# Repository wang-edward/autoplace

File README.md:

# Autoplace
This is a kicad plugin to help in the intial layout of a board. It "solves" a component placement by minimizing wirelength while smoothing out density.

This isn't meant to one-shot a component layout, but as a helpful first step to group related components.

**It works best when Edge.Cuts is well defined, and static components (like ports) are locked.**

## Installation
Symlink `autoplace/` into the plugins folder:

### MacOS
```bash
ln -s "$(pwd)/autoplace" ~/Documents/KiCad/10.0/plugins/autoplace  # KiCad 10
```

### Linux
```bash
ln -s "$(pwd)/autoplace" ~/.local/share/KiCad/10.0/plugins/autoplace  # KiCad 10
```

The idea is based on the DreamPlace algorithm: https://github.com/limbo018/DREAMPlace

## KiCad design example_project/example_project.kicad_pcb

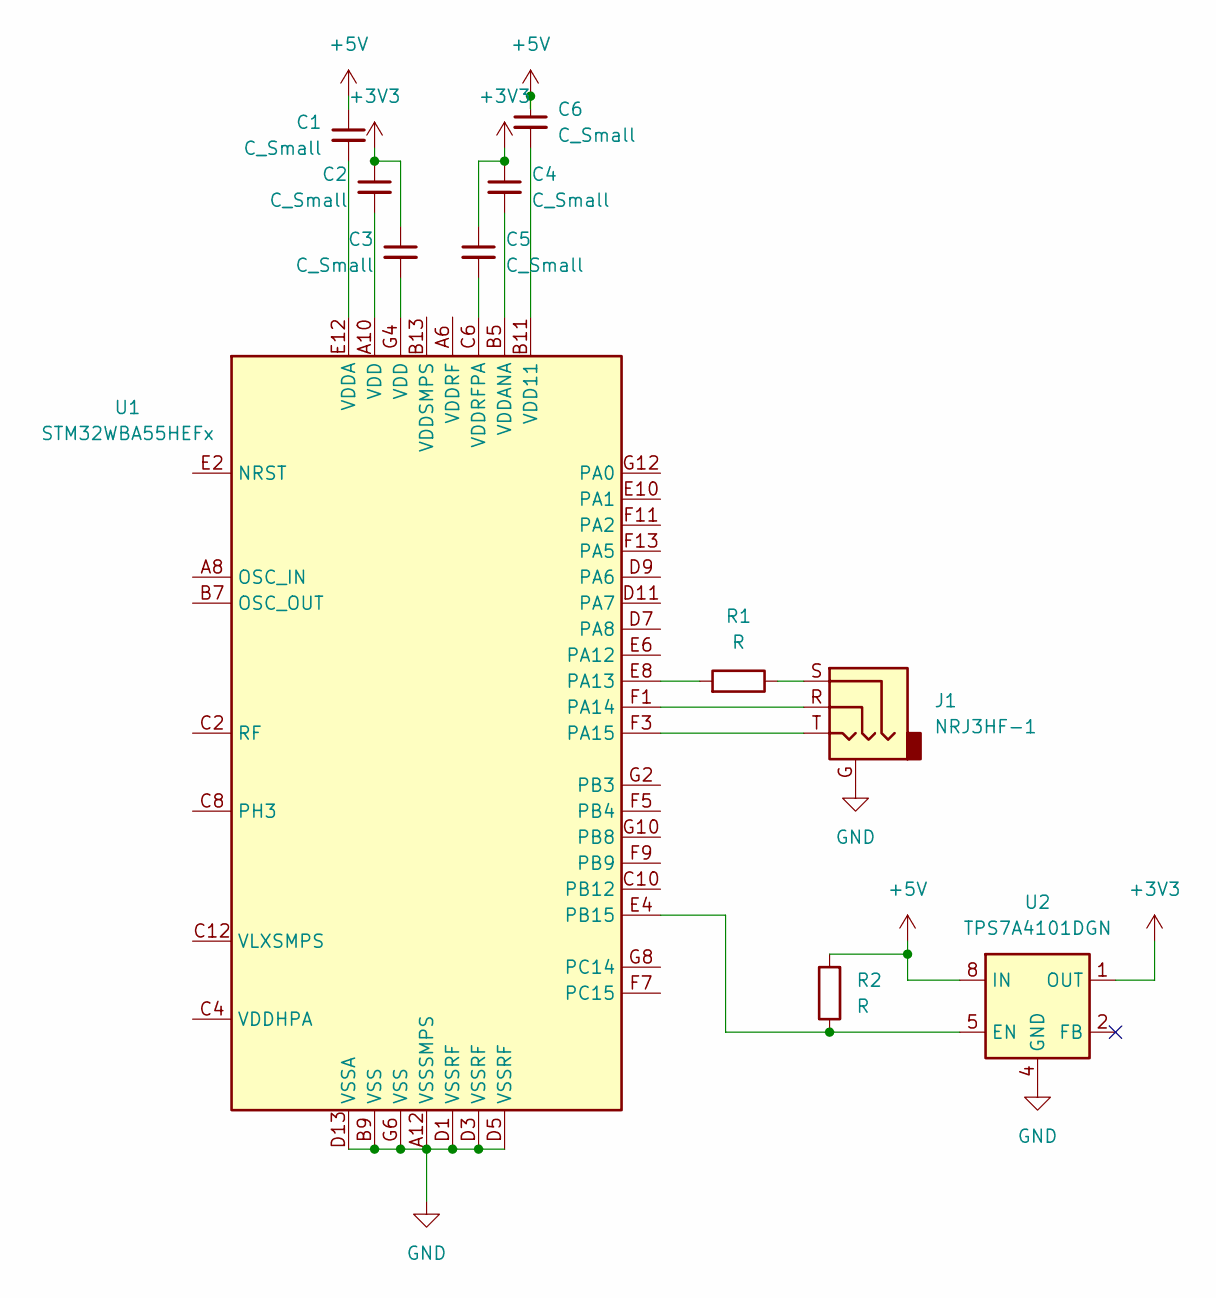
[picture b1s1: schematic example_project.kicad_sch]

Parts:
C1, C2, C3, C4, C5, C6: C_Small; C_0805_2012Metric
J1: NRJ3HF-1; Jack_6.35mm_Neutrik_NRJ3HF-1_Horizontal
R1, R2: R; R_0805_2012Metric
U1: STM32WBA55HEFx; ST_WLCSP-41_2.98x2.76mm_Layout13x7_P0.4mm_Stagger
U2: TPS7A4101DGN; Texas_DGN0008B_VSSOP-8-1EP_3x3mm_P0.65mm_EP2x3mm_Mask1.88x1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

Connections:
+3V3: C2.1, C3.1, C4.1, C5.1, U2.1 (OUT)
+5V: C1.1, C6.1, R2.2, U2.8 (IN)
GND: J1.G, U1.A12 (VSSSMPS), U1.B9 (VSS), U1.D1 (VSSRF), U1.D3 (VSSRF), U1.D5 (VSSRF), U1.D13 (VSSA), U1.G6 (VSS), U2.4 (GND), U2.9 (GND)
unnamed: C2.2, U1.A10 (VDD)
unnamed: C3.2, U1.G4 (VDD)
unnamed: J1.S, R1.1
unnamed: R1.2, U1.E8 (PA13)
unnamed: J1.R, U1.F1 (PA14)
unnamed: J1.T, U1.F3 (PA15)
unnamed: R2.1, U1.E4 (PB15), U2.5 (EN)
unnamed: C6.2, U1.B11 (VDD11)
unnamed: C1.2, U1.E12 (VDDA)
unnamed: C4.2, U1.B5 (VDDANA)
unnamed: C5.2, U1.C6 (VDDRFPA)

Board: 2 copper layers, 11 parts (0 on the bottom side), 14 nets, no tracks yet.

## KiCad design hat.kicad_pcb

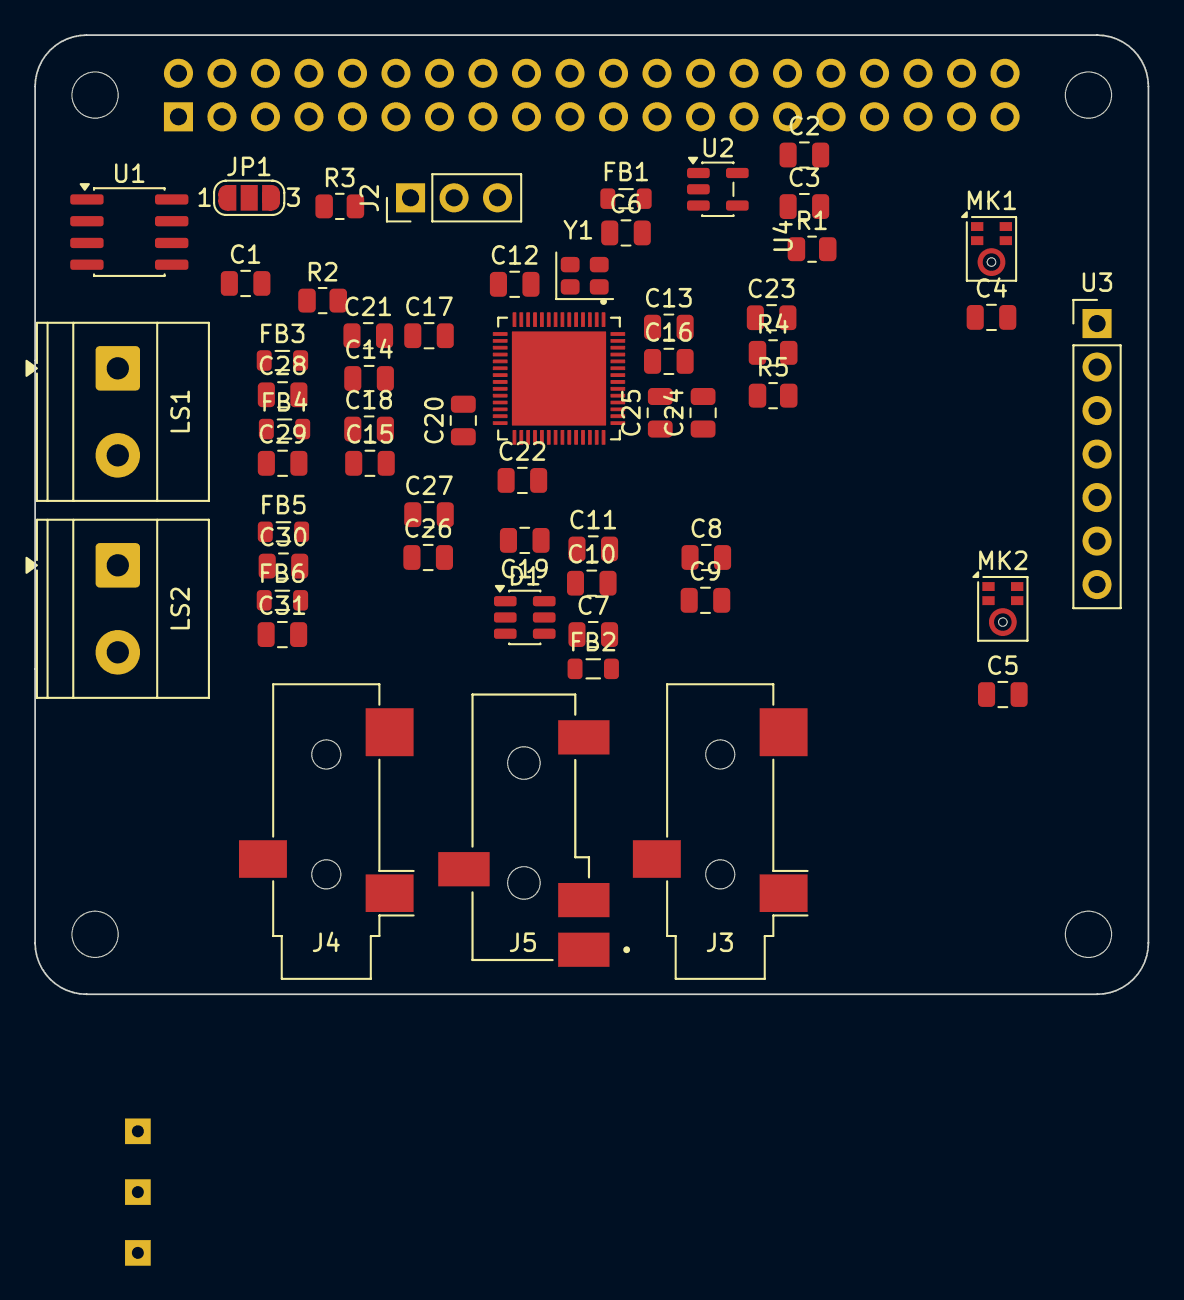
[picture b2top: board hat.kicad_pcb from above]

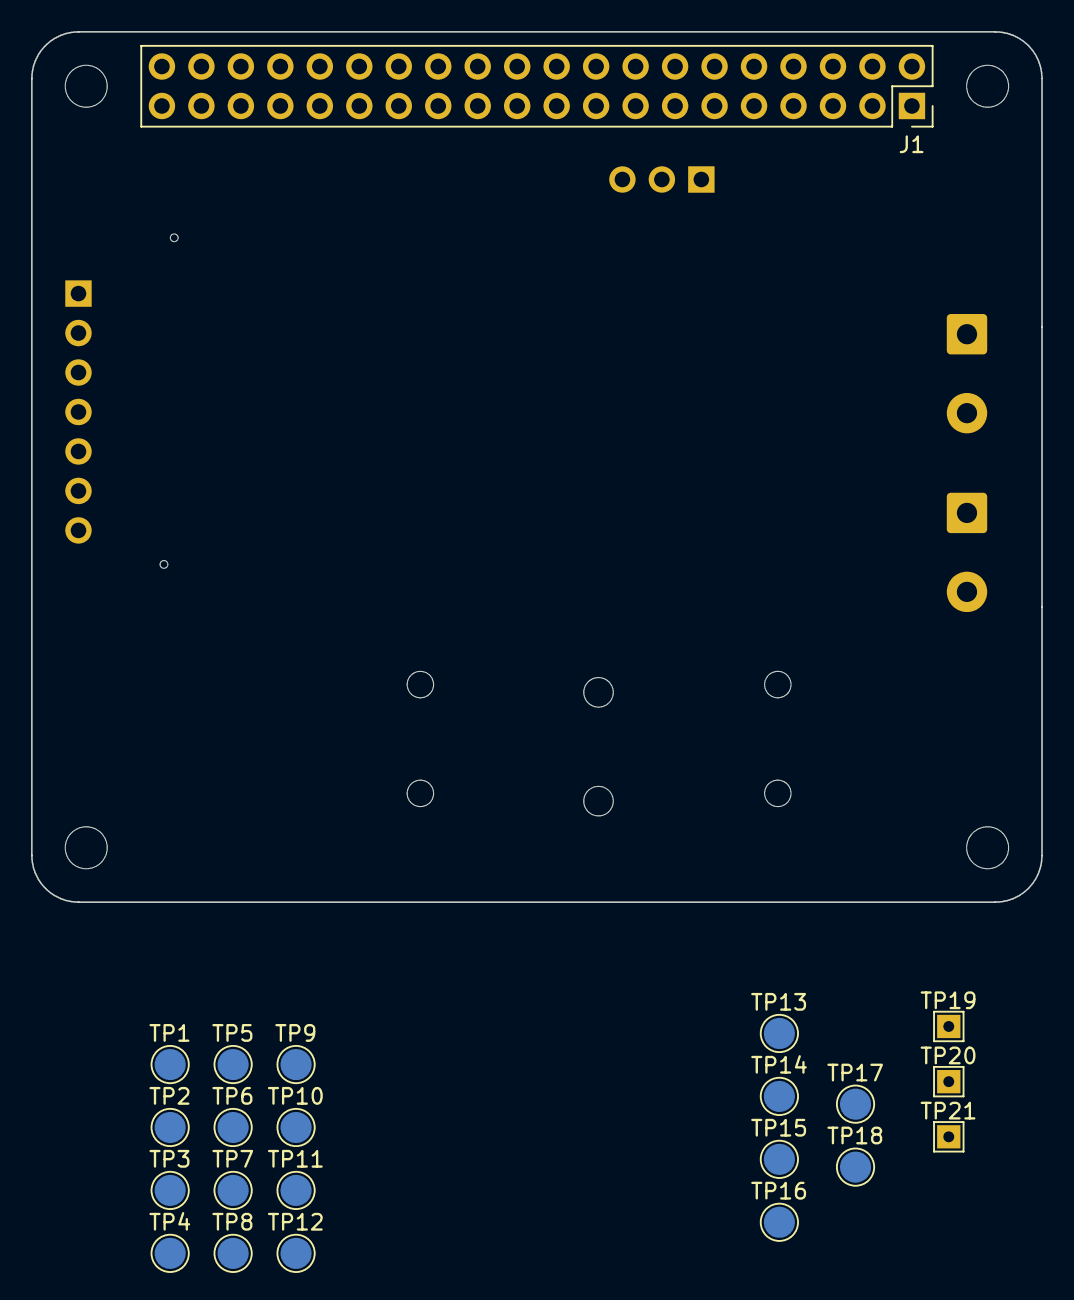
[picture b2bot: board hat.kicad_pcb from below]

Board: 2 copper layers, 65.0 x 56.0 mm, 83 parts (22 on the bottom side), 56 nets, no tracks yet.

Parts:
C1: 100n; C_0805_2012Metric
C2, C3, C8, C9, C10, C11, C13, C15, C16, C18, C19, C20, C21, C22, C24: 1uF; C_0805_2012Metric
C4, C5, C6: 0.1uF X7R; C_0805_2012Metric
C7: 47pF; C_0805_2012Metric
C12, C23: 0.1uF; C_0805_2012Metric
C14, C17, C26, C27: 10uF; C_0805_2012Metric
C25: 2.2uF; C_0805_2012Metric
C28, C29, C30, C31: 470pF; C_0805_2012Metric
D1: ESDA6V1BC6; SOT-23-6
FB1, FB2, FB3, FB4, FB5, FB6: 600Ohm@100MHz; L_0805_2012Metric
J1: GPIO; PinSocket_2x20_P2.54mm_Vertical
J2: Uart; PinHeader_1x03_P2.54mm_Vertical
J3: LineIn; Jack_3.5mm_CUI_SJ-3523-SMT_Horizontal
J4: LineOut; Jack_3.5mm_CUI_SJ-3523-SMT_Horizontal
J5: Headphone; CUI_SJ-43514-SMT-TR
JP1: ID_WP; SolderJumper-3_P1.3mm_Open_RoundedPad1.0x1.5mm_NumberLabels
LS1: SpeakerL; TerminalBlock_Phoenix_MKDS-1,5-2-5.08_1x02_P5.08mm_Horizont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
LS2: SpeakerR; TerminalBlock_Phoenix_MKDS-1,5-2-5.08_1x02_P5.08mm_Horizont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
MH1, MH2, MH3, MH4: MountingHole_2.7mm_M2.5
MK1: MicL; Knowles_LGA-5_3.5x2.65mm
MK2: MicR; Knowles_LGA-5_3.5x2.65mm
R1, R4: 10k; R_0805_2012Metric
R2, R3: 3.9k; R_0805_2012Metric
R5: 2.2k; R_0805_2012Metric
TP1: MICBIAS; TestPoint_Pad_D2.0mm
TP2: INA1; TestPoint_Pad_D2.0mm
TP3: INA2; TestPoint_Pad_D2.0mm
TP4: CODEC_MCLK; TestPoint_Pad_D2.0mm
TP5: MIC2P; TestPoint_Pad_D2.0mm
TP6: MIC2N; TestPoint_Pad_D2.0mm
TP7: HPSNS; TestPoint_Pad_D2.0mm
TP8: HPR; TestPoint_Pad_D2.0mm
TP9: HPL; TestPoint_Pad_D2.0mm
TP10: JACKSENSE; TestPoint_Pad_D2.0mm
TP11: RECP; TestPoint_Pad_D2.0mm
TP12: RECN; TestPoint_Pad_D2.0mm
TP13: SPKLP; TestPoint_Pad_D2.0mm
TP14: SPKLN; TestPoint_Pad_D2.0mm
TP15: SPKRP; TestPoint_Pad_D2.0mm
TP16: SPKRN; TestPoint_Pad_D2.0mm
TP17: LDO_IN; TestPoint_Pad_D2.0mm
TP18: LDO_OUT; TestPoint_Pad_D2.0mm
TP19: 5V; TestPoint_THTPad_1.5x1.5mm_Drill0.7mm
TP20: GND; TestPoint_THTPad_1.5x1.5mm_Drill0.7mm
TP21: 3V3; TestPoint_THTPad_1.5x1.5mm_Drill0.7mm
U1: CAT24C256; SOIC-8_3.9x4.9mm_P1.27mm
U2: TPS7A20xxxDBV; SOT-23-5
U3: Oled; PinHeader_1x07_P2.54mm_Vertical
U4: MAX98089ETN_T
Y1: 12.288MHz; Oscillator_SMD_SeikoEpson_SG210-4Pin_2.5x2.0mm

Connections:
+1V8: C3.1, C4.2, C5.2, C13.2, C14.2, C15.2, C16.2, MK1.5 (VDD), MK2.2 (SEL), MK2.5 (VDD), TP18.1 (1_1), U2.5 (OUT), U4.25 (PVDD), U4.50 (AVDD), U4.53 (DVDD)
+3V3: C1.1, C2.1, C12.2, C23.2, FB1.2, J1.1, J1.17, JP1.2 (B), R2.1, R3.1, R4.2, TP17.1 (1_1), TP21.1 (1_1), U1.8 (VCC), U2.1 (IN), U3.1 (VCC), U4.6 (DVDDS1), U4.55 (DVDDS2)
+5V: C17.2, C18.2, C21.2, J1.2, J1.4, TP19.1 (1_1), U4.18 (SPKRVDD), U4.19 (SPKLVDD)
/1V8_EN: J1.16, R1.1, U2.3 (EN)
/GPIO2/SDA1: J1.3, U4.52 (SDA)
/GPIO3/SCL1: J1.5, U4.51 (SCL)
/GPIO8/SPI0.CE0: J1.24, U3.5 (CS)
/GPIO10/SPI0.MOSI: J1.19, U3.3 (DIN)
/GPIO11/SPI0.SCLK: J1.23, U3.4 (CLK)
/GPIO14/TXD0: J1.8, J2.2
/GPIO15/RXD0: J1.10, J2.3
/GPIO17: J1.11, R4.1, U4.56 (~IRQ)
/GPIO18/PCM.CLK: J1.12, U4.8 (BCLKS1)
/GPIO19/PCM.FS: J1.35, U4.10 (LRCLKS1)
/GPIO20/PCM.DIN: J1.38, U4.7 (SDOUTS1)
/GPIO21/PCM.DOUT: J1.40, U4.9 (SDINS1)
/GPIO22: J1.15, Y1.1 (OE)
/GPIO25: J1.22, U3.6 (DC)
/GPIO27: J1.13, U3.7 (RST)
/ID_SCL: J1.28, R3.2, U1.6 (SCL)
/ID_SDA: J1.27, R2.2, U1.5 (SDA)
/codec/C1N: C20.1, U4.27 (C1N)
/codec/C1P: C20.2, U4.26 (C1P)
/codec/DIGMICCLK: MK1.4 (CLOCK), MK2.4 (CLOCK), U4.41 (MIC1N/DIGMICCLK)
/codec/DIGMICDATA: MK1.1 (DATA), MK2.1 (DATA), U4.40 (MIC1P/DIGMICDATA)
/codec/JackS: D1.6 (TVS4), FB2.1, J5.S, R5.2, TP1.1 (1_1), TP10.1 (1_1), U4.45 (JACKSNS)
GND: C1.2, C2.2, C3.2, C4.1, C5.1, C6.1, C7.2, C11.1, C12.1, C13.1, C14.1, C15.1, C16.1, C17.1, C18.1, C19.2, C21.1, C22.2, C23.1, C24.2, C25.2, C28.2, C29.2, C30.2, C31.2, D1.2 (COM), D1.4 (TVS3), D1.5 (COM), J1.6, J1.9, J1.14, J1.20, J1.25, J1.30, J1.34, J1.39, J2.1, J3.S, J4.S, J5.R2, MK1.2 (SEL), MK1.3 (GND), MK2.3 (GND), R1.2, TP7.1 (1_1), TP20.1 (1_1), U1.4 (GND), U2.2 (GND), U3.2 (GND), U4.3 (DGND), U4.16 (SPKRGND), U4.21 (SPKLGND), U4.30 (HPGND), U4.34 (HPSNS), U4.47 (AGND), U4.54 (SDINS2), U4.57 (EP), Y1.2 (GND)
unnamed: C8.1, J3.T
unnamed: C9.1, J3.R
unnamed: C7.1, C10.1, FB2.2
unnamed: C26.2, J4.T, TP11.1 (1_1)
unnamed: C27.2, J4.R, TP12.1 (1_1)
unnamed: C28.1, FB3.2, LS1.1, TP13.1 (1_1)
unnamed: C29.1, FB4.2, LS1.2, TP14.1 (1_1)
unnamed: C30.1, FB5.2, LS2.1, TP15.1 (1_1)
unnamed: C31.1, FB6.2, LS2.2, TP16.1 (1_1)
unnamed: D1.1 (TVS1), J5.T, TP9.1 (1_1), U4.33 (HPL)
unnamed: D1.3 (TVS2), J5.R1, TP8.1 (1_1), U4.35 (HPR)
unnamed: JP1.1 (A), U1.7 (WP)
unnamed: C22.1, U4.32 (HPVDD)
unnamed: C19.1, U4.31 (HPVSS)
unnamed: C10.2, TP5.1 (1_1), U4.39 (INA1/EXTMICP)
unnamed: C11.2, TP6.1 (1_1), U4.38 (INA2/EXTMICN)
unnamed: TP4.1 (1_1), U4.5 (MCLK), Y1.3 (OUT)
unnamed: C9.2, TP3.1 (1_1), U4.43 (MIC2N)
unnamed: C8.2, TP2.1 (1_1), U4.42 (MIC2P)
unnamed: R5.1, U4.44 (MICBIAS)
unnamed: C27.1, U4.23 (RECN/LOUTR/RXINN)
unnamed: C26.1, U4.24 (RECP/LOUTL/RXINP)
unnamed: C25.1, U4.48 (REF)
unnamed: C24.1, U4.49 (REG)
unnamed: FB4.1, U4.22 (SPKLN)
unnamed: FB3.1, U4.20 (SPKLP)
unnamed: FB6.1, U4.15 (SPKRN)
unnamed: FB5.1, U4.17 (SPKRP)
unnamed: C6.2, FB1.1, Y1.4 (Vcc)

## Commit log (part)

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2026-05-24 less code
2026-05-30 kicad import
2026-06-12 uv init and notebook
2026-06-12 attract
2026-06-12 wa_wirelength
2026-06-12 vibe
2026-06-12 vibe 2
2026-06-12 big thing and fixed
2026-06-12 wip theta
2026-06-12 something
2026-06-16 gitignore
2026-06-16 clean
2026-06-16 hello
2026-06-16 print
2026-06-16 get_edge_cuts
2026-06-16 get_components
2026-06-16 make example more complicated
2026-06-16 wip plugin
2026-06-16 desc2
2026-06-16 plugin showing up in toolbar!!!!!!!!!!!!!!!!!!
2026-06-17 torch notebook
2026-06-17 make example more compl
2026-06-18 finally working!
2026-06-18 notebook -> script
2026-06-18 make wx dialog
2026-06-18 wip custom dialog
2026-06-19 rename
2026-06-19 clea
2026-06-19 Add title and highlight Edge.Cuts importance
    Added a title and emphasized the importance of Edge.Cuts and locked components.
2026-06-19 Update README with installation instructions and algorithm reference
    Added reference to the DreamPlace algorithm as the basis for the plugin.
